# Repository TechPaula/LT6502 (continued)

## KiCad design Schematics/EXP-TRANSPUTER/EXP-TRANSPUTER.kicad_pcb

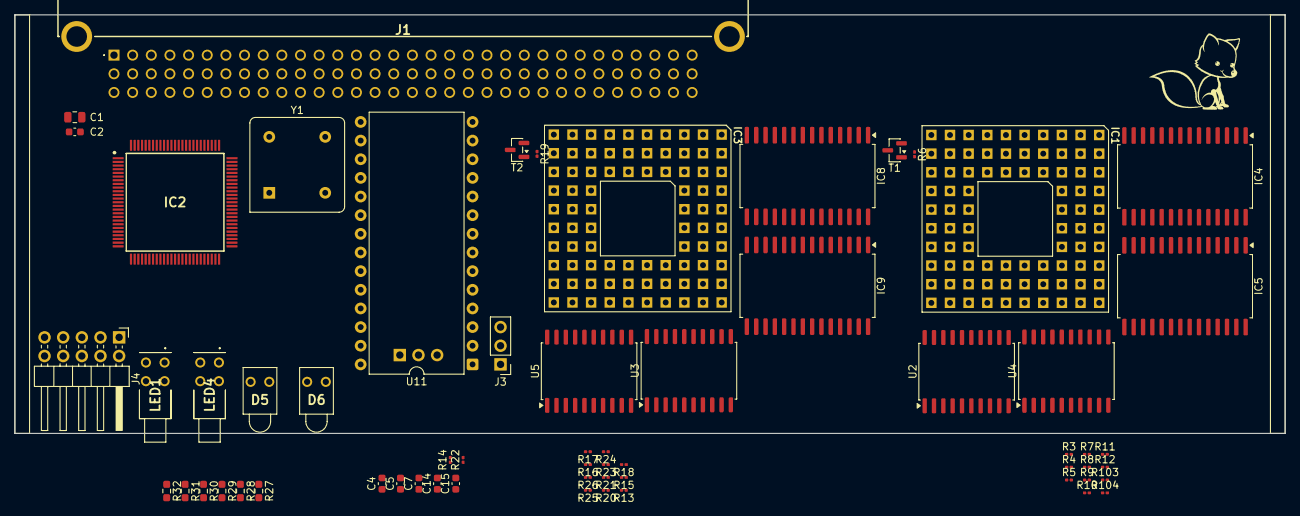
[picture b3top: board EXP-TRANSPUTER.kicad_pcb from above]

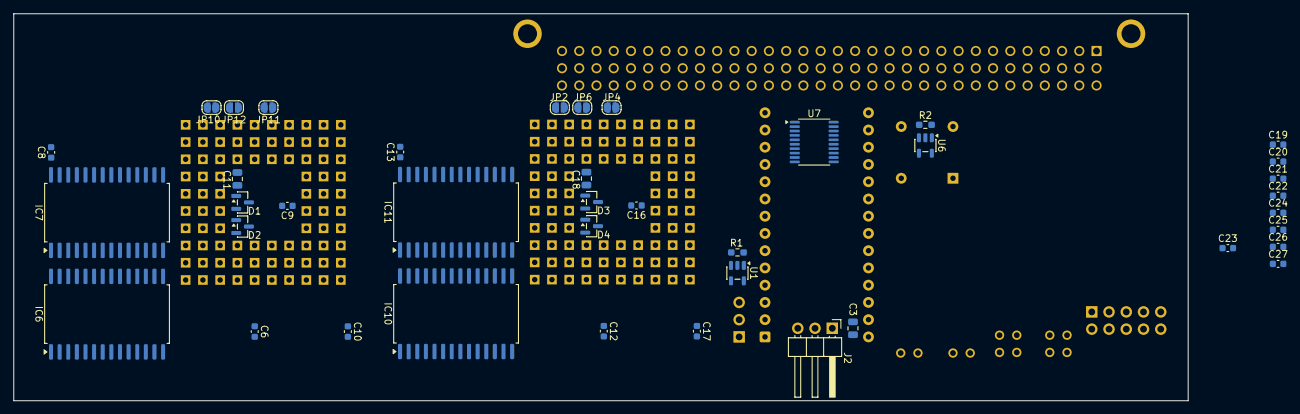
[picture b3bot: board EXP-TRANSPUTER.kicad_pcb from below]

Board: 2 copper layers, 173.0 x 57.0 mm, 102 parts (40 on the bottom side), 177 nets, no tracks yet.

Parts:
C1: 22uF 25V; C_0805_2012Metric
C2, C4, C5, C7, C14, C15, C19, C20, C21, C22, C23, C24, C25, C26, C27: 100nF; C_0603_1608Metric
C3: 1uF 10V; C_0805_2012Metric
C6, C8, C9, C10, C12, C13, C16, C17: 100n; C_0603_1608Metric
C11, C18: 1u; C_0805_2012Metric
D1, D2, D3, D4: BAV70; SOT-23
D5, D6: LED; LTL4221NHBP
FOX1: SYM_Flash_Large; Fox_avatar_18mm
IC1, IC3: IMST800; PGA84
IC2: ATF1508AS-7AX100; QFP50P1600X1600X120-100N
IC4, IC5, IC6, IC7, IC8, IC9, IC10, IC11: CY62256N; SOP-28_8.4x18.16mm_P1.27mm
J1: DIN41612_02x32_AC(CAPS); 86093967113745ELF
J2: Conn_01x03; PinHeader_1x03_P2.54mm_Horizontal
J3: Conn_01x03; PinHeader_1x03_P2.54mm_Vertical
J4: Conn_02x05_Odd_Even; PinHeader_2x05_P2.54mm_Horizontal
JP2, JP4, JP6, JP10, JP11, JP12: Jumper_2_Open; SolderJumper-2_P1.3mm_Open_RoundedPad1.0x1.5mm
LED1, LED4: LTL-42D1NMHDP1; LTL42D1NMHDP1
R1, R2: 10K; R_0603_1608Metric_Pad0.98x0.95mm_HandSolder
R3, R4, R5, R6, R7, R8, R13, R15, R16, R17, R18, R19, R20, R21, R103, R104: 10k; R_0201_0603Metric
R9, R10, R11, R12, R23, R24, R25, R26: 56; R_0201_0603Metric
R14: 10K; R_0201_0603Metric
R22: 3K3; R_0201_0603Metric
R27, R28, R29, R30, R31, R32: 470R; R_0603_1608Metric_Pad0.98x0.95mm_HandSolder
T1, T2: BC847; SOT-23
U1, U6: SN74LVC1G125DBV; SOT-23-5
U2, U3, U4, U5: 74HC373; SOIC-20W_7.5x12.8mm_P1.27mm
U7: SN74LV245APW; TSSOP-20_4.4x6.5mm_P0.65mm
U11: IMSC011; DIP-28_W15.24mm
Y1: CXO_DIP8; Oscillator_DIP-8

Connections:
5MHz_INT: U6.2, U11.15 (ClockIn), Y1.5 (OUT)
+5V: C1.1, C2.1, C3.1, C4.1, C5.1, C6.1, C7.1, C8.1, C9.1, C10.1, C12.1, C13.1, C14.1, C15.1, C16.1, C17.1, C19.1, C20.1, C21.1, C22.1, C23.1, C24.1, C25.1, C26.1, C27.1, D1.3 (C), D2.3 (C), D3.3 (C), D4.3 (C), IC1.A2 (LINKSPECIAL), IC1.C2 (VCC@0), IC1.C5 (VCC@1), IC1.E10 (VCC@2), IC1.H4 (VCC@3), IC3.A2 (LINKSPECIAL), IC3.C2 (VCC@0), IC3.C5 (VCC@1), IC3.E10 (VCC@2), IC3.H4 (VCC@3), IC4.28 (VCC), IC5.28 (VCC), IC6.28 (VCC), IC7.28 (VCC), IC8.28 (VCC), IC9.28 (VCC), IC10.28 (VCC), IC11.28 (VCC), J1.A2, J1.A31, J1.C2, J1.C31, J2.1, J4.4, R8.1, R16.1, R17.1, R21.1, R22.1, R29.1, R30.2, R31.1, R32.2, R103.1, R104.1, U1.5 (VCC), U2.20 (VCC), U3.20 (VCC), U4.20 (VCC), U5.20 (VCC), U6.5 (VCC), U7.20 (VCC), U11.28 (VCC), Y1.8 (Vcc)
/Connector/A0: J1.C18, U11.5 (RS0)
/Connector/A1: J1.A18, U11.6 (RS1)
/Connector/D0: J1.C20, U7.2 (A1)
/Connector/D1: J1.A20, U7.3 (A2)
/Connector/D2: J1.C21, U7.4 (A3)
/Connector/D3: J1.A21, U7.5 (A4)
/Connector/D4: J1.C22, U7.6 (A5)
/Connector/D5: J1.A22, U7.7 (A6)
/Connector/D6: J1.C23, U7.8 (A7)
/Connector/D7: J1.A23, U7.9 (A8)
/LinkAdapter/5MHz_OUT: IC1.B2 (CLKIN), IC3.B2 (CLKIN), U6.4
/LinkAdapter/LINKADAP_nCS: R22.2, U7.19 (~OE), U11.25 (notCS)
/LinkAdapter/SPEED_OUT: IC1.A4 (LINKSPEED123), IC1.B4 (LINKSPEED0), IC3.A4 (LINKSPEED123), IC3.B4 (LINKSPEED0), J2.2, U11.17 (LinkSpeed)
/TRAMOnBoard1/A2: IC8.10 (A0), IC9.10 (A0), IC10.10 (A0), IC11.10 (A0), U3.2 (O0)
/TRAMOnBoard1/A3: IC8.9 (A1), IC9.9 (A1), IC10.9 (A1), IC11.9 (A1), U3.12 (O4)
/TRAMOnBoard1/A4: IC8.8 (A2), IC9.8 (A2), IC10.8 (A2), IC11.8 (A2), U5.16 (O6)
/TRAMOnBoard1/A5: IC8.7 (A3), IC9.7 (A3), IC10.7 (A3), IC11.7 (A3), U3.6 (O2)
/TRAMOnBoard1/A6: IC8.6 (A4), IC9.6 (A4), IC10.6 (A4), IC11.6 (A4), U3.9 (O3)
/TRAMOnBoard1/A7: IC8.5 (A5), IC9.5 (A5), IC10.5 (A5), IC11.5 (A5), U3.19 (O7)
/TRAMOnBoard1/A8: IC8.4 (A6), IC9.4 (A6), IC10.4 (A6), IC11.4 (A6), U3.16 (O6)
/TRAMOnBoard1/A9: IC8.3 (A7), IC9.3 (A7), IC10.3 (A7), IC11.3 (A7), U3.15 (O5)
/TRAMOnBoard1/A10: IC8.25 (A8), IC9.25 (A8), IC10.25 (A8), IC11.25 (A8), U3.5 (O1)
/TRAMOnBoard1/A11: IC8.24 (A9), IC9.24 (A9), IC10.24 (A9), IC11.24 (A9), U5.15 (O5)
/TRAMOnBoard1/A12: IC8.21 (A10), IC9.21 (A10), IC10.21 (A10), IC11.21 (A10), U5.2 (O0)
/TRAMOnBoard1/A13: IC8.23 (A11), IC9.23 (A11), IC10.23 (A11), IC11.23 (A11), U5.5 (O1)
/TRAMOnBoard1/A14: IC8.2 (A12), IC9.2 (A12), IC10.2 (A12), IC11.2 (A12), U5.12 (O4)
/TRAMOnBoard1/A15: IC8.26 (A13), IC9.26 (A13), IC10.26 (A13), IC11.26 (A13), U5.6 (O2)
/TRAMOnBoard1/A16: IC8.1 (A14), IC9.1 (A14), IC10.1 (A14), IC11.1 (A14), U5.9 (O3)
/TRAMOnBoard1/AD0: IC3.G8 (NOTMEMWRD0), IC8.17 (I/O5)
/TRAMOnBoard1/AD1: IC3.H10 (NOTMEMRFD1), IC8.13 (I/O2)
/TRAMOnBoard1/AD2: IC3.J10 (MEMAD2), IC8.12 (I/O1), U3.3 (D0)
/TRAMOnBoard1/AD3: IC3.H9 (MEMAD3), IC8.18 (I/O6), U3.13 (D4)
/TRAMOnBoard1/AD4: IC3.H8 (MEMAD4), IC8.15 (I/O3), U5.17 (D6)
/TRAMOnBoard1/AD5: IC3.J9 (MEMAD5), IC8.19 (I/O7), U3.7 (D2)
/TRAMOnBoard1/AD6: IC3.J8 (MEMAD6), IC8.16 (I/O4), U3.8 (D3)
/TRAMOnBoard1/AD7: IC3.K10 (MEMAD7), IC8.11 (I/O0), U3.18 (D7)
/TRAMOnBoard1/AD8: IC3.C8 (MEMCONFIG), IC3.H7 (MEMAD8), IC9.11 (I/O0), U3.17 (D6)
/TRAMOnBoard1/AD9: IC3.K9 (MEMAD9), IC9.13 (I/O2), U3.14 (D5)
/TRAMOnBoard1/AD10: IC3.K8 (MEMAD10), IC9.12 (I/O1), U3.4 (D1)
/TRAMOnBoard1/AD11: IC3.K7 (MEMAD11), IC9.15 (I/O3), U5.14 (D5)
/TRAMOnBoard1/AD12: IC3.H6 (MEMAD12), IC9.16 (I/O4), U5.3 (D0)
/TRAMOnBoard1/AD13: IC3.J6 (MEMAD13), IC9.17 (I/O5), U5.4 (D1)
/TRAMOnBoard1/AD14: IC3.K6 (MEMAD14), IC9.18 (I/O6), U5.13 (D4)
/TRAMOnBoard1/AD15: IC3.K5 (MEMAD15), IC9.19 (I/O7), U5.7 (D2)
/TRAMOnBoard1/AD16: IC3.H5 (MEMAD16), IC10.12 (I/O1), U5.8 (D3)
/TRAMOnBoard1/AD17: IC3.J5 (MEMAD17), IC10.11 (I/O0)
/TRAMOnBoard1/AD18: IC3.K4 (MEMAD18), IC10.13 (I/O2)
/TRAMOnBoard1/AD19: IC3.J4 (MEMAD19), IC10.19 (I/O7)
/TRAMOnBoard1/AD20: IC3.K3 (MEMAD20), IC10.16 (I/O4)
/TRAMOnBoard1/AD21: IC3.K2 (MEMAD21), IC10.15 (I/O3)
/TRAMOnBoard1/AD22: IC3.J3 (MEMAD22), IC10.17 (I/O5)
/TRAMOnBoard1/AD23: IC3.H3 (MEMAD23), IC10.18 (I/O6)
/TRAMOnBoard1/AD24: IC3.J2 (MEMAD24), IC11.11 (I/O0)
/TRAMOnBoard1/AD25: IC3.H2 (MEMAD25), IC11.12 (I/O1)
/TRAMOnBoard1/AD26: IC3.K1 (MEMAD26), IC11.15 (I/O3)
/TRAMOnBoard1/AD27: IC3.G3 (MEMAD27), IC11.13 (I/O2)
/TRAMOnBoard1/AD28: IC3.J1 (MEMAD28), IC11.16 (I/O4)
/TRAMOnBoard1/AD29: IC3.H1 (MEMAD29), IC11.17 (I/O5)
/TRAMOnBoard1/AD30: IC3.G1 (MEMAD30), IC11.18 (I/O6)
/TRAMOnBoard1/AD31: IC3.F3 (MEMAD31), IC11.19 (I/O7)
/TRAMOnBoard1/E: IC3.E9 (NOTMEMS0), IC8.20 (~CS), IC9.20 (~CS), IC10.20 (~CS), IC11.20 (~CS)
/TRAMOnBoard1/LINK1_IN: D4.1 (A1), IC3.C6 (LINKIN1), R15.2
/TRAMOnBoard1/LINK2_IN: D4.2 (A2), IC3.A7 (LINKIN2), R20.2
/TRAMOnBoard1/LINK3_IN: D3.2 (A2), IC3.C7 (LINKIN3), R18.2
/TRAMOnBoard1/RD: IC3.E8 (NOTMEMRD), IC8.22 (~OE), IC9.22 (~OE), IC10.22 (~OE), IC11.22 (~OE)
/TRAMOnBoard1/WR0: IC3.D10 (NOTMEMWRB0), IC8.27 (~WE)
/TRAMOnBoard1/WR1: IC3.C10 (NOTMEMWRB1), IC9.27 (~WE)
/TRAMOnBoard1/WR2: IC3.D9 (NOTMEMWRB2), IC10.27 (~WE)
/TRAMOnBoard1/WR3: IC3.B10 (NOTMEMWRB3), IC11.27 (~WE)
/TRAMOnBoard/A2: IC4.10 (A0), IC5.10 (A0), IC6.10 (A0), IC7.10 (A0), U4.2 (O0)
/TRAMOnBoard/A3: IC4.9 (A1), IC5.9 (A1), IC6.9 (A1), IC7.9 (A1), U4.12 (O4)
/TRAMOnBoard/A4: IC4.8 (A2), IC5.8 (A2), IC6.8 (A2), IC7.8 (A2), U2.16 (O6)
/TRAMOnBoard/A5: IC4.7 (A3), IC5.7 (A3), IC6.7 (A3), IC7.7 (A3), U4.6 (O2)
/TRAMOnBoard/A6: IC4.6 (A4), IC5.6 (A4), IC6.6 (A4), IC7.6 (A4), U4.9 (O3)
/TRAMOnBoard/A7: IC4.5 (A5), IC5.5 (A5), IC6.5 (A5), IC7.5 (A5), U4.19 (O7)
/TRAMOnBoard/A8: IC4.4 (A6), IC5.4 (A6), IC6.4 (A6), IC7.4 (A6), U4.16 (O6)
/TRAMOnBoard/A9: IC4.3 (A7), IC5.3 (A7), IC6.3 (A7), IC7.3 (A7), U4.15 (O5)
/TRAMOnBoard/A10: IC4.25 (A8), IC5.25 (A8), IC6.25 (A8), IC7.25 (A8), U4.5 (O1)
/TRAMOnBoard/A11: IC4.24 (A9), IC5.24 (A9), IC6.24 (A9), IC7.24 (A9), U2.15 (O5)
/TRAMOnBoard/A12: IC4.21 (A10), IC5.21 (A10), IC6.21 (A10), IC7.21 (A10), U2.2 (O0)
/TRAMOnBoard/A13: IC4.23 (A11), IC5.23 (A11), IC6.23 (A11), IC7.23 (A11), U2.5 (O1)
/TRAMOnBoard/A14: IC4.2 (A12), IC5.2 (A12), IC6.2 (A12), IC7.2 (A12), U2.12 (O4)
/TRAMOnBoard/A15: IC4.26 (A13), IC5.26 (A13), IC6.26 (A13), IC7.26 (A13), U2.6 (O2)
/TRAMOnBoard/A16: IC4.1 (A14), IC5.1 (A14), IC6.1 (A14), IC7.1 (A14), U2.9 (O3)
/TRAMOnBoard/AD0: IC1.G8 (NOTMEMWRD0), IC4.17 (I/O5)
/TRAMOnBoard/AD1: IC1.H10 (NOTMEMRFD1), IC4.13 (I/O2)
/TRAMOnBoard/AD2: IC1.J10 (MEMAD2), IC4.12 (I/O1), U4.3 (D0)
/TRAMOnBoard/AD3: IC1.H9 (MEMAD3), IC4.18 (I/O6), U4.13 (D4)
/TRAMOnBoard/AD4: IC1.H8 (MEMAD4), IC4.15 (I/O3), U2.17 (D6)
/TRAMOnBoard/AD5: IC1.J9 (MEMAD5), IC4.19 (I/O7), U4.7 (D2)
/TRAMOnBoard/AD6: IC1.J8 (MEMAD6), IC4.16 (I/O4), U4.8 (D3)
/TRAMOnBoard/AD7: IC1.K10 (MEMAD7), IC4.11 (I/O0), U4.18 (D7)
/TRAMOnBoard/AD8: IC1.C8 (MEMCONFIG), IC1.H7 (MEMAD8), IC5.11 (I/O0), U4.17 (D6)
/TRAMOnBoard/AD9: IC1.K9 (MEMAD9), IC5.13 (I/O2), U4.14 (D5)
/TRAMOnBoard/AD10: IC1.K8 (MEMAD10), IC5.12 (I/O1), U4.4 (D1)
/TRAMOnBoard/AD11: IC1.K7 (MEMAD11), IC5.15 (I/O3), U2.14 (D5)
/TRAMOnBoard/AD12: IC1.H6 (MEMAD12), IC5.16 (I/O4), U2.3 (D0)
/TRAMOnBoard/AD13: IC1.J6 (MEMAD13), IC5.17 (I/O5), U2.4 (D1)
/TRAMOnBoard/AD14: IC1.K6 (MEMAD14), IC5.18 (I/O6), U2.13 (D4)
/TRAMOnBoard/AD15: IC1.K5 (MEMAD15), IC5.19 (I/O7), U2.7 (D2)
/TRAMOnBoard/AD16: IC1.H5 (MEMAD16), IC6.12 (I/O1), U2.8 (D3)
/TRAMOnBoard/AD17: IC1.J5 (MEMAD17), IC6.11 (I/O0)
/TRAMOnBoard/AD18: IC1.K4 (MEMAD18), IC6.13 (I/O2)
/TRAMOnBoard/AD19: IC1.J4 (MEMAD19), IC6.19 (I/O7)
/TRAMOnBoard/AD20: IC1.K3 (MEMAD20), IC6.16 (I/O4)
/TRAMOnBoard/AD21: IC1.K2 (MEMAD21), IC6.15 (I/O3)
/TRAMOnBoard/AD22: IC1.J3 (MEMAD22), IC6.17 (I/O5)
/TRAMOnBoard/AD23: IC1.H3 (MEMAD23), IC6.18 (I/O6)
/TRAMOnBoard/AD24: IC1.J2 (MEMAD24), IC7.11 (I/O0)
/TRAMOnBoard/AD25: IC1.H2 (MEMAD25), IC7.12 (I/O1)
/TRAMOnBoard/AD26: IC1.K1 (MEMAD26), IC7.15 (I/O3)
/TRAMOnBoard/AD27: IC1.G3 (MEMAD27), IC7.13 (I/O2)
/TRAMOnBoard/AD28: IC1.J1 (MEMAD28), IC7.16 (I/O4)
/TRAMOnBoard/AD29: IC1.H1 (MEMAD29), IC7.17 (I/O5)
/TRAMOnBoard/AD30: IC1.G1 (MEMAD30), IC7.18 (I/O6)
/TRAMOnBoard/AD31: IC1.F3 (MEMAD31), IC7.19 (I/O7)
/TRAMOnBoard/E: IC1.E9 (NOTMEMS0), IC4.20 (~CS), IC5.20 (~CS), IC6.20 (~CS), IC7.20 (~CS)
/TRAMOnBoard/LINK2_IN: D2.2 (A2), IC1.A7 (LINKIN2), R7.2
/TRAMOnBoard/LINK3_IN: D1.2 (A2), IC1.C7 (LINKIN3), R5.2
/TRAMOnBoard/RD: IC1.E8 (NOTMEMRD), IC4.22 (~OE), IC5.22 (~OE), IC6.22 (~OE), IC7.22 (~OE)
/TRAMOnBoard/WR0: IC1.D10 (NOTMEMWRB0), IC4.27 (~WE)
/TRAMOnBoard/WR1: IC1.C10 (NOTMEMWRB1), IC5.27 (~WE)
/TRAMOnBoard/WR2: IC1.D9 (NOTMEMWRB2), IC6.27 (~WE)
/TRAMOnBoard/WR3: IC1.B10 (NOTMEMWRB3), IC7.27 (~WE)
GND: C1.2, C2.2, C4.2, C5.2, C6.2, C7.2, C8.2, C9.2, C10.2, C12.2, C13.2, C14.2, C15.2, C16.2, C17.2, C19.2, C20.2, C21.2, C22.2, C23.2, C24.2, C25.2, C26.2, C27.2, IC1.A9 (GND@0), IC1.A10 (MEMWAIT), IC1.B8 (EVENTREQ), IC1.B9 (MEMREQ), IC1.C1 (GND@1), IC1.D3 (ERRIN), IC1.E1 (DISABLEINTRAM), IC1.E2 (BOOTFROMROM), IC1.G2 (GND@2), IC1.G9 (GND@3), IC1.J7 (GND@4), IC3.A9 (GND@0), IC3.A10 (MEMWAIT), IC3.B8 (EVENTREQ), IC3.B9 (MEMREQ), IC3.C1 (GND@1), IC3.D3 (ERRIN), IC3.E1 (DISABLEINTRAM), IC3.E2 (BOOTFROMROM), IC3.G2 (GND@2), IC3.G9 (GND@3), IC3.J7 (GND@4), IC4.14 (VSS), IC5.14 (VSS), IC6.14 (VSS), IC7.14 (VSS), IC8.14 (VSS), IC9.14 (VSS), IC10.14 (VSS), IC11.14 (VSS), J1.A1, J1.A6, J1.A10, J1.A19, J1.A32, J1.C1, J1.C6, J1.C10, J1.C19, J1.C32, J2.3, J3.1, J4.2, J4.10, JP2.2 (B), JP4.2 (B), JP6.2 (B), JP10.2 (B), JP11.2 (B), JP12.2 (B), R1.2, R2.2, R3.1, R4.1, R5.1, R7.1, R13.1, R14.2, R15.1, R18.1, R20.1, T1.2 (E), T2.2 (E), U1.3 (GND), U2.1 (OE), U2.10 (GND), U2.18 (D7), U3.1 (OE), U3.10 (GND), U4.1 (OE), U4.10 (GND), U5.1 (OE), U5.10 (GND), U5.18 (D7), U6.3 (GND), U7.10 (GND), U11.11 (HoldToGND), U11.14 (GND), U11.16 (SeparateIQ), Y1.4 (GND)
LA_LINK_IN: J3.2, R9.2, R14.1, U11.2 (LinkIn)
LA_LINK_OUT: D1.1 (A1), IC1.A5 (LINKIN0), J3.3, R3.2, U1.4
LA_TRAM0_IN: D2.1 (A1), IC1.C6 (LINKIN1), R4.2, R23.2
LA_TRAM0_OUT: D3.1 (A1), IC3.A5 (LINKIN0), R10.2, R13.2
unnamed: D5.2 (A), R27.1
unnamed: D6.2 (A), R28.1
unnamed: C11.1, IC1.C4 (CAP+)
unnamed: C11.2, IC1.C3 (CAP-)
unnamed: IC1.D1 (ERROUT), R6.1
unnamed: IC1.B5 (LINKOUT0), R9.1
unnamed: IC1.A6 (LINKOUT1), R10.1
unnamed: IC1.B6 (LINKOUT2), R11.1
unnamed: IC1.B7 (LINKOUT3), R12.1
unnamed: IC1.G10 (NOTMEMS1), U2.11 (LE), U4.11 (LE)
unnamed: IC1.B1 (PROCSPEED0), JP10.1 (A), R103.2
unnamed: IC1.F1 (PROCSPEED1), JP11.1 (A), R104.2
unnamed: IC1.D2 (PROCSPEED2), JP12.1 (A), R8.2
unnamed: C18.1, IC3.C4 (CAP+)
unnamed: C18.2, IC3.C3 (CAP-)
unnamed: IC3.D1 (ERROUT), R19.1
unnamed: IC3.B5 (LINKOUT0), R23.1
unnamed: IC3.A6 (LINKOUT1), R24.1
unnamed: IC3.B6 (LINKOUT2), R25.1
unnamed: IC3.B7 (LINKOUT3), R26.1
unnamed: IC3.G10 (NOTMEMS1), U3.11 (LE), U5.11 (LE)
unnamed: IC3.B1 (PROCSPEED0), JP2.1 (A), R16.2
unnamed: IC3.F1 (PROCSPEED1), JP4.1 (A), R17.2
unnamed: IC3.D2 (PROCSPEED2), JP6.1 (A), R21.2
unnamed: LED1.2 (A_1), R32.1
unnamed: LED1.4 (A_2), R31.2
unnamed: LED4.2 (A_1), R30.1
unnamed: LED4.4 (A_2), R29.2
unnamed: R1.1, U1.1
unnamed: R2.1, U6.1
unnamed: R27.2, R28.2
unnamed: R6.2, T1.1 (B)
unnamed: R19.2, T2.1 (B)
unnamed: C3.2, U11.27 (CapMinus)
unnamed: U7.18 (B1), U11.24 (D0)
unnamed: U7.17 (B2), U11.23 (D1)
unnamed: U7.16 (B3), U11.22 (D2)
unnamed: U7.15 (B4), U11.8 (D3)
unnamed: U7.14 (B5), U11.20 (D4)
unnamed: U7.13 (B6), U11.10 (D5)
unnamed: U7.12 (B7), U11.18 (D6)
unnamed: U7.11 (B8), U11.12 (D7)
unnamed: U1.2, U11.1 (LinkOut)
TRAM_nANALYSE: D6.1 (K), IC1.F2 (ANALYSE), IC3.F2 (ANALYSE)
TRAM_nERROR: D5.1 (K), T1.3 (C), T2.3 (C)
TRAM_nRESET: IC1.E3 (RESET), IC3.E3 (RESET)

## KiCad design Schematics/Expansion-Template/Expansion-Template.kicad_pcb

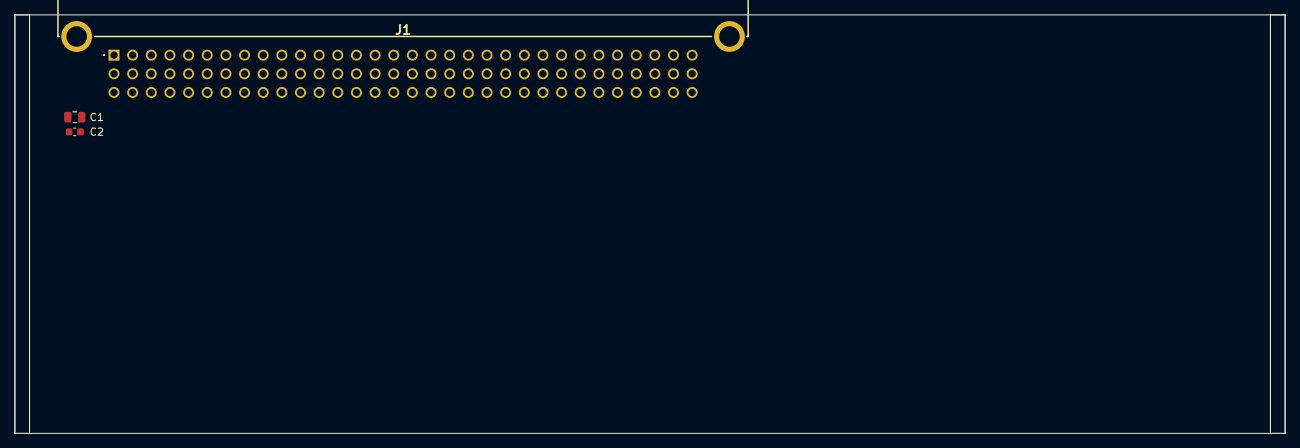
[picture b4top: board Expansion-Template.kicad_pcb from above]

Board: 2 copper layers, 173.0 x 57.0 mm, 3 parts (0 on the bottom side), 2 nets, no tracks yet.

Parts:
C1: 22uF 25V; C_0805_2012Metric
C2: 100nF; C_0603_1608Metric
J1: DIN41612_02x32_AC(CAPS); 86093967113745ELF

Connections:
+5V: C1.1, C2.1, J1.A2, J1.A31, J1.C2, J1.C31
GND: C1.2, C2.2, J1.A1, J1.A6, J1.A10, J1.A19, J1.A32, J1.C1, J1.C6, J1.C10, J1.C19, J1.C32

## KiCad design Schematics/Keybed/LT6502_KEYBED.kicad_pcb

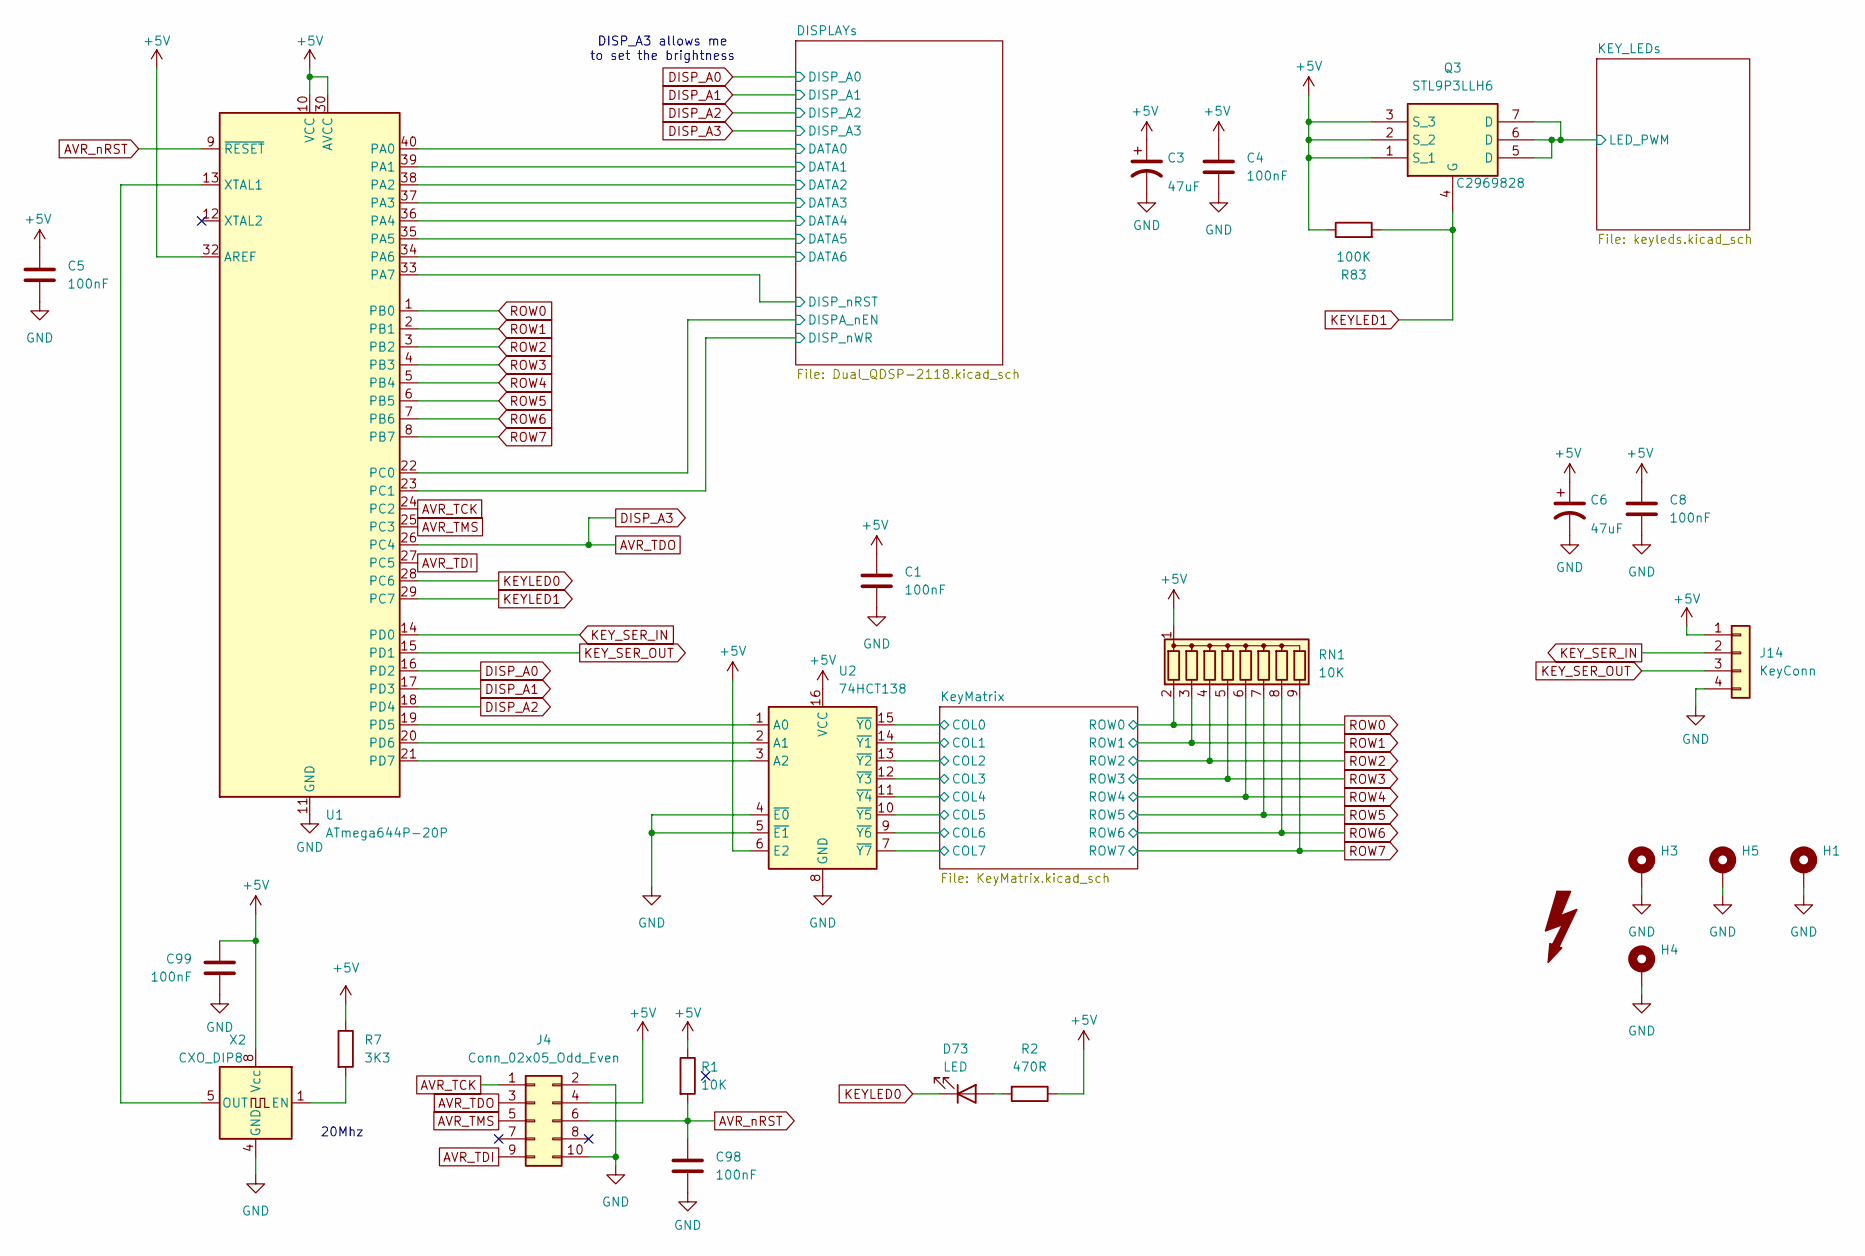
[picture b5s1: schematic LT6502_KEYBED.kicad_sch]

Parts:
C1, C4, C5, C8, C98, C99: 100nF; C_0805_2012Metric; LCSC C49678
C3, C6: 47uF; C_1206_3216Metric; LCSC C96123
D73: LED; LED_D5.0mm; LCSC DNF
FOX1: SYM_Flash_Large; Fox_avatar_18mm; LCSC DNF
H1, H3, H4, H5: MountingHole_Pad; MountingHole_3.2mm_M3_Pad_TopBottom; LCSC DNF
J4: Conn_02x05_Odd_Even; PinHeader_2x05_P2.54mm_Horizontal; LCSC DNF
J14: KeyConn; PinHeader_1x04_P2.54mm_Horizontal; LCSC DNF
Q3: STL9P3LLH6; STL20N6F7; Manufacturer_Part_Number STL9P3LLH6; Mouser Part Number 511-STL9P3LLH6
R1: 10K; R_0603_1608Metric_Pad0.98x0.95mm_HandSolder; LCSC DNF
R2: 470R; R_0603_1608Metric_Pad0.98x0.95mm_HandSolder; LCSC DNF
R7: 3K3; R_0603_1608Metric_Pad0.98x0.95mm_HandSolder; LCSC DNF
R83: 100K; R_0402_1005Metric; LCSC DNF
RN1: 10K; R_Array_SIP9; LCSC DNF
U1: ATmega644P-20P; DIP-40_W15.24mm; LCSC DNF
U2: 74HCT138; SSOP-16_5.3x6.2mm_P0.65mm; LCSC C8115
X2: CXO_DIP8; Oscillator_DIP-8; LCSC DNF

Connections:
+5V: C1.1, C3.1, C4.1, C5.1, C6.1, C8.1, C99.1, J4.4, J14.1, Q3.1 (S_1), Q3.2 (S_2), Q3.3 (S_3), R1.1, R2.1, R7.1, R83.1, RN1.1 (common), U1.10 (VCC), U1.30 (AVCC), U1.32 (AREF), U2.6 (E2), U2.16 (VCC), X2.8 (Vcc); also elsewhere on the board
/DISPLAYs/DATA0: U1.40 (PA0); also elsewhere on the board
/DISPLAYs/DATA1: U1.39 (PA1); also elsewhere on the board
/DISPLAYs/DATA2: U1.38 (PA2); also elsewhere on the board
/DISPLAYs/DATA3: U1.37 (PA3); also elsewhere on the board
/DISPLAYs/DATA4: U1.36 (PA4); also elsewhere on the board
/DISPLAYs/DATA5: U1.35 (PA5); also elsewhere on the board
/DISPLAYs/DATA6: U1.34 (PA6); also elsewhere on the board
/DISPLAYs/DISPA_nEN: U1.22 (PC0); also elsewhere on the board
/DISPLAYs/DISP_nRST: U1.33 (PA7); also elsewhere on the board
/DISPLAYs/DISP_nWR: U1.23 (PC1); also elsewhere on the board
/KEY_LEDs/LED_PWM: Q3.5 (D), Q3.6 (D), Q3.7 (D); also elsewhere on the board
/KeyMatrix/COL0: U2.15 (~Y0); also elsewhere on the board
/KeyMatrix/COL1: U2.14 (~Y1); also elsewhere on the board
/KeyMatrix/COL2: U2.13 (~Y2); also elsewhere on the board
/KeyMatrix/COL3: U2.12 (~Y3); also elsewhere on the board
/KeyMatrix/COL4: U2.11 (~Y4); also elsewhere on the board
/KeyMatrix/COL5: U2.10 (~Y5); also elsewhere on the board
/KeyMatrix/COL6: U2.9 (~Y6); also elsewhere on the board
/KeyMatrix/COL7: U2.7 (~Y7); also elsewhere on the board
AVR_TCK: J4.1, U1.24 (PC2)
AVR_TDI: J4.9, U1.27 (PC5)
AVR_TDO: J4.3, U1.26 (PC4); also elsewhere on the board
AVR_TMS: J4.5, U1.25 (PC3)
AVR_nRST: C98.1, J4.6, R1.2, U1.9 (~RESET)
DISP_A0: U1.16 (PD2); also elsewhere on the board
DISP_A1: U1.17 (PD3); also elsewhere on the board
DISP_A2: U1.18 (PD4); also elsewhere on the board
GND: C1.2, C3.2, C4.2, C5.2, C6.2, C8.2, C98.2, C99.2, H1.1, H3.1, H4.1, H5.1, J4.2, J4.10, J14.4, U1.11 (GND), U1.31 (GND), U2.4 (~E0), U2.5 (~E1), U2.8 (GND), X2.4 (GND); also elsewhere on the board
KEYLED0: D73.1 (K), U1.28 (PC6)
KEYLED1: Q3.4 (G), R83.2, U1.29 (PC7)
KEY_SER_IN: J14.2, U1.14 (PD0)
KEY_SER_OUT: J14.3, U1.15 (PD1)
unnamed: D73.2 (A), R2.2
unnamed: U1.19 (PD5), U2.1 (A0)
unnamed: U1.20 (PD6), U2.2 (A1)
unnamed: U1.21 (PD7), U2.3 (A2)
unnamed: U1.13 (XTAL1), X2.5 (OUT)
unnamed: R7.2, X2.1 (EN)
ROW0: RN1.2 (R1), U1.1 (PB0); also elsewhere on the board
ROW1: RN1.3 (R2), U1.2 (PB1); also elsewhere on the board
ROW2: RN1.4 (R3), U1.3 (PB2); also elsewhere on the board
ROW3: RN1.5 (R4), U1.4 (PB3); also elsewhere on the board
ROW4: RN1.6 (R5), U1.5 (PB4); also elsewhere on the board
ROW5: RN1.7 (R6), U1.6 (PB5); also elsewhere on the board
ROW6: RN1.8 (R7), U1.7 (PB6); also elsewhere on the board
ROW7: RN1.9 (R8), U1.8 (PB7); also elsewhere on the board

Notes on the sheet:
20Mhz
DISP_A3 allows me to set the brightness

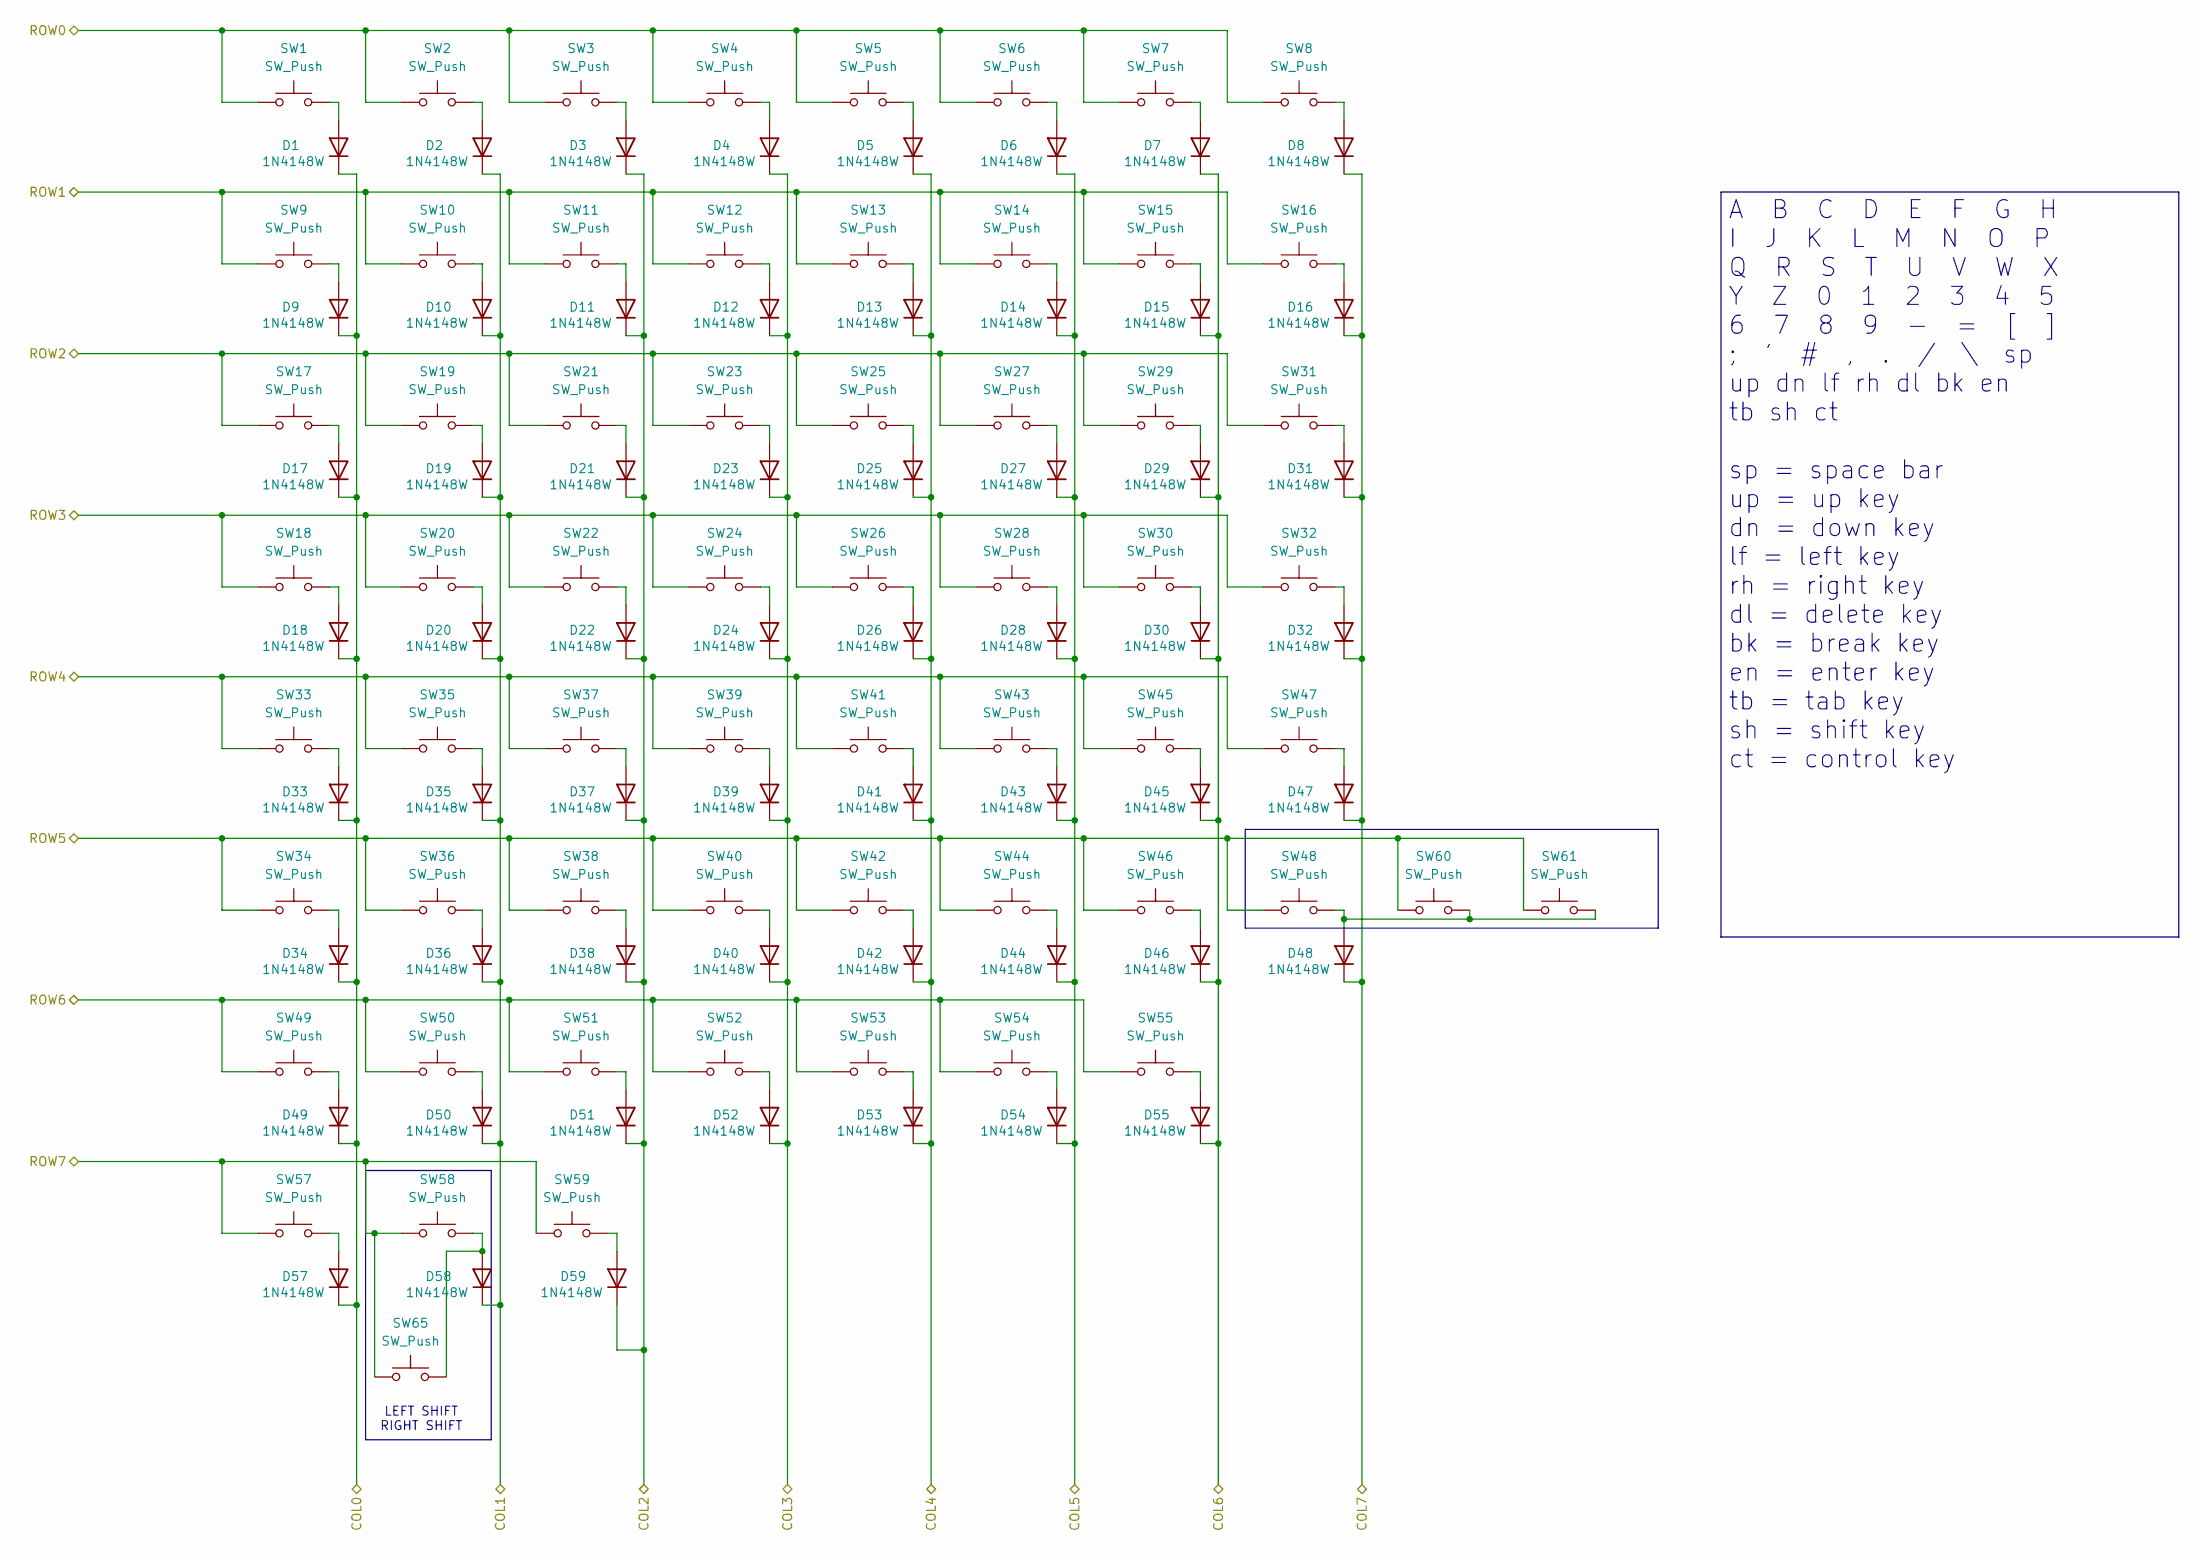
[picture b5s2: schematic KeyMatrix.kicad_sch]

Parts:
D1, D2, D3, D4, D5, D6, D7, D8, D9, D10, D11, D12, D13, D14, D15, D16, D17, D18, D19, D20, D21, D22, D23, D24, D25, D26, D27, D28, D29, D30, D31, D32, D33, D34, D35, D36, D37, D38, D39, D40, D41, D42, D43, D44, D45, D46, D47, D48, D49, D50, D51, D52, D53, D54, D55, D57, D58, D59: 1N4148W; D_SOD-123; LCSC C2099
SW1, SW2, SW3, SW4, SW5, SW6, SW7, SW8, SW9, SW10, SW11, SW12, SW13, SW14, SW15, SW16, SW17, SW18, SW19, SW20, SW21, SW22, SW23, SW24, SW25, SW26, SW27, SW28, SW29, SW30, SW31, SW32, SW33, SW34, SW35, SW36, SW37, SW38, SW39, SW40, SW41, SW42, SW43, SW44, SW45, SW46, SW47, SW48, SW49, SW50, SW51, SW52, SW53, SW54, SW55, SW57, SW58, SW59, SW60, SW61, SW65: SW_Push; SW_PG1350; LCSC DNF

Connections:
/KeyMatrix/COL0: D1.1 (K), D9.1 (K), D17.1 (K), D18.1 (K), D33.1 (K), D34.1 (K), D49.1 (K), D57.1 (K); also elsewhere on the board
/KeyMatrix/COL1: D2.1 (K), D10.1 (K), D19.1 (K), D20.1 (K), D35.1 (K), D36.1 (K), D50.1 (K), D58.1 (K); also elsewhere on the board
/KeyMatrix/COL2: D3.1 (K), D11.1 (K), D21.1 (K), D22.1 (K), D37.1 (K), D38.1 (K), D51.1 (K), D59.1 (K); also elsewhere on the board
/KeyMatrix/COL3: D4.1 (K), D12.1 (K), D23.1 (K), D24.1 (K), D39.1 (K), D40.1 (K), D52.1 (K); also elsewhere on the board
/KeyMatrix/COL4: D5.1 (K), D13.1 (K), D25.1 (K), D26.1 (K), D41.1 (K), D42.1 (K), D53.1 (K); also elsewhere on the board
/KeyMatrix/COL5: D6.1 (K), D14.1 (K), D27.1 (K), D28.1 (K), D43.1 (K), D44.1 (K), D54.1 (K); also elsewhere on the board
/KeyMatrix/COL6: D7.1 (K), D15.1 (K), D29.1 (K), D30.1 (K), D45.1 (K), D46.1 (K), D55.1 (K); also elsewhere on the board
/KeyMatrix/COL7: D8.1 (K), D16.1 (K), D31.1 (K), D32.1 (K), D47.1 (K), D48.1 (K); also elsewhere on the board
unnamed: D1.2 (A), SW1.2
unnamed: D2.2 (A), SW2.2
unnamed: D3.2 (A), SW3.2
unnamed: D4.2 (A), SW4.2
unnamed: D5.2 (A), SW5.2
unnamed: D6.2 (A), SW6.2
unnamed: D7.2 (A), SW7.2
unnamed: D8.2 (A), SW8.2
unnamed: D9.2 (A), SW9.2
unnamed: D10.2 (A), SW10.2
unnamed: D11.2 (A), SW11.2
unnamed: D12.2 (A), SW12.2
unnamed: D13.2 (A), SW13.2
unnamed: D14.2 (A), SW14.2
unnamed: D15.2 (A), SW15.2
unnamed: D16.2 (A), SW16.2
unnamed: D17.2 (A), SW17.2
unnamed: D18.2 (A), SW18.2
unnamed: D19.2 (A), SW19.2
unnamed: D20.2 (A), SW20.2
unnamed: D21.2 (A), SW21.2
unnamed: D22.2 (A), SW22.2
unnamed: D23.2 (A), SW23.2
unnamed: D24.2 (A), SW24.2
unnamed: D25.2 (A), SW25.2
unnamed: D26.2 (A), SW26.2
unnamed: D27.2 (A), SW27.2
unnamed: D28.2 (A), SW28.2
unnamed: D29.2 (A), SW29.2
unnamed: D30.2 (A), SW30.2
unnamed: D31.2 (A), SW31.2
unnamed: D32.2 (A), SW32.2
unnamed: D33.2 (A), SW33.2
unnamed: D34.2 (A), SW34.2
unnamed: D35.2 (A), SW35.2
unnamed: D36.2 (A), SW36.2
unnamed: D37.2 (A), SW37.2
unnamed: D38.2 (A), SW38.2
unnamed: D39.2 (A), SW39.2
unnamed: D40.2 (A), SW40.2
unnamed: D41.2 (A), SW41.2
unnamed: D42.2 (A), SW42.2
unnamed: D43.2 (A), SW43.2
unnamed: D44.2 (A), SW44.2
unnamed: D45.2 (A), SW45.2
unnamed: D46.2 (A), SW46.2
unnamed: D47.2 (A), SW47.2
unnamed: D48.2 (A), SW48.2, SW60.2, SW61.2
unnamed: D49.2 (A), SW49.2
unnamed: D50.2 (A), SW50.2
unnamed: D51.2 (A), SW51.2
unnamed: D52.2 (A), SW52.2
unnamed: D53.2 (A), SW53.2
unnamed: D54.2 (A), SW54.2
unnamed: D55.2 (A), SW55.2
unnamed: D57.2 (A), SW57.2
unnamed: D58.2 (A), SW58.2, SW65.2
unnamed: D59.2 (A), SW59.2
ROW0: SW1.1, SW2.1, SW3.1, SW4.1, SW5.1, SW6.1, SW7.1, SW8.1; also elsewhere on the board
ROW1: SW9.1, SW10.1, SW11.1, SW12.1, SW13.1, SW14.1, SW15.1, SW16.1; also elsewhere on the board
ROW2: SW17.1, SW19.1, SW21.1, SW23.1, SW25.1, SW27.1, SW29.1, SW31.1; also elsewhere on the board
ROW3: SW18.1, SW20.1, SW22.1, SW24.1, SW26.1, SW28.1, SW30.1, SW32.1; also elsewhere on the board
ROW4: SW33.1, SW35.1, SW37.1, SW39.1, SW41.1, SW43.1, SW45.1, SW47.1; also elsewhere on the board
ROW5: SW34.1, SW36.1, SW38.1, SW40.1, SW42.1, SW44.1, SW46.1, SW48.1, SW60.1, SW61.1; also elsewhere on the board
ROW6: SW49.1, SW50.1, SW51.1, SW52.1, SW53.1, SW54.1, SW55.1; also elsewhere on the board
ROW7: SW57.1, SW58.1, SW59.1, SW65.1; also elsewhere on the board

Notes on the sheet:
LEFT SHIFT RIGHT SHIFT
A B C D E F G H I J K L M N O P Q R S T U V W X Y Z 0 1 2 3 4 5 6 7 8 9 - = [ ] ; ' # , . / \ sp up dn lf rh dl bk en tb sh ct sp = space bar up = up key dn = down key lf = left key rh = right key dl = delete key bk = break key en = enter key tb = tab key sh = shift key ct = control key

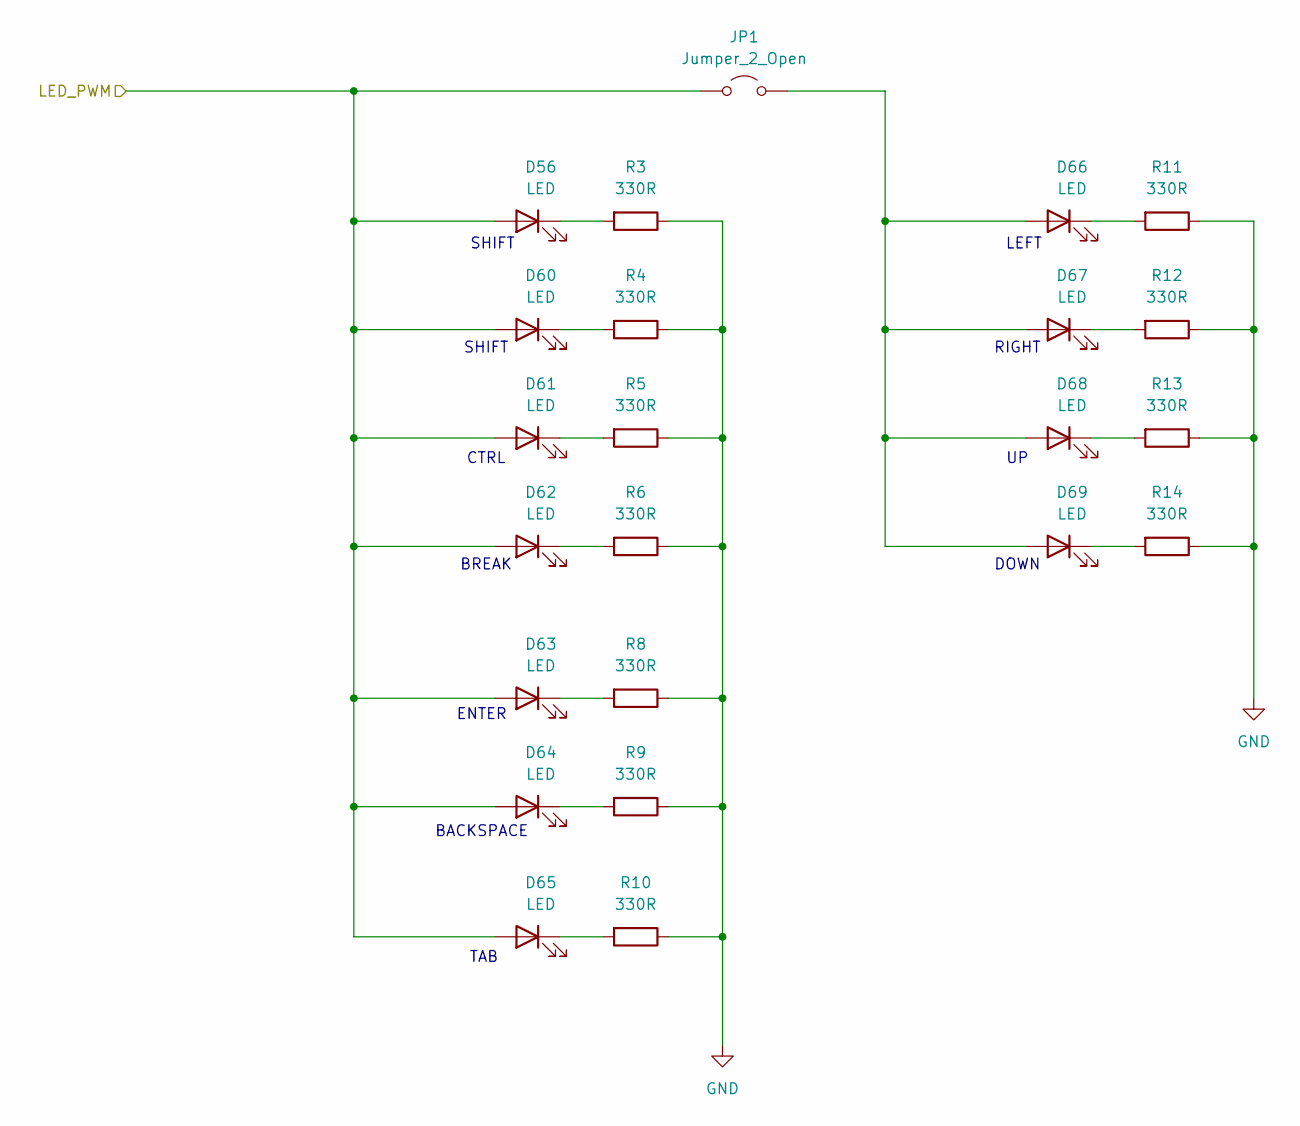
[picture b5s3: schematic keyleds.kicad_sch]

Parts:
D56, D60, D61, D62, D63, D64, D65, D66, D67, D68, D69: LED; LED_0603_1608Metric; LCSC C3030991
JP1: Jumper_2_Open; SolderJumper-2_P1.3mm_Open_TrianglePad1.0x1.5mm; LCSC DNF
R3, R4, R5, R6, R8, R9, R10, R11, R12, R13, R14: 330R; R_0603_1608Metric_Pad0.98x0.95mm_HandSolder; LCSC DNF

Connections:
/KEY_LEDs/LED_PWM: D56.2 (A), D60.2 (A), D61.2 (A), D62.2 (A), D63.2 (A), D64.2 (A), D65.2 (A), JP1.1 (A); also elsewhere on the board
GND: R3.1, R4.1, R5.1, R6.1, R8.1, R9.1, R10.1, R11.1, R12.1, R13.1, R14.1; also elsewhere on the board
unnamed: D56.1 (K), R3.2
unnamed: D60.1 (K), R4.2
unnamed: D61.1 (K), R5.2
unnamed: D62.1 (K), R6.2
unnamed: D63.1 (K), R8.2
unnamed: D64.1 (K), R9.2
unnamed: D65.1 (K), R10.2
unnamed: D66.2 (A), D67.2 (A), D68.2 (A), D69.2 (A), JP1.2 (B)
unnamed: D66.1 (K), R11.2
unnamed: D67.1 (K), R12.2
unnamed: D68.1 (K), R13.2
unnamed: D69.1 (K), R14.2

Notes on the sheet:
BREAK
TAB
SHIFT
DOWN
CTRL
LEFT
RIGHT
BACKSPACE
ENTER
